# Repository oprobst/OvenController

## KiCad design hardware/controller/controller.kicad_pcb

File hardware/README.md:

# Hardware

KiCad-Projekte des Ofen-Controllers. Entscheidungen und Begründungen:
`specs/002-controller-pcb/plan.md` und `research.md`, Werkzeugwahl: `docs/werkzeuge-pcb.md`.

| Verzeichnis | Inhalt |
|---|---|
| `lib/` | projekteigene Symbole (`oven.kicad_sym`) und Footprints (`oven.pretty/`), Prüfliste in `lib/README.md` |
| `controller/` | Hauptplatine REV A: Schaltplan (`controller.kicad_sch` + 2 Blätter: `controller_leistung` (A3: Netzteil, Sicherheit, Last) und `controller_steuerung` (A2: MCU, USB, Thermoelemente, Bedienung)), Platine, Designregeln, Referenznetzliste `controller.ref.net`, Exporte in `output/` |
| `encoder-carrier/` | Encoder-Träger REV A, gleiche Struktur |
| `tools/` | Prüf- und Hilfsskripte (siehe unten) |
| `archive/skidl/` | früherer Schaltplan als SKiDL-Code (nur noch Archiv) |

## Werkzeugkette

- **Quelle ist der KiCad-10-Schaltplan.** KiCad 10.0.3 unter `D:\hobby\Elektronik\KiCad\10.0`,
  Kommandozeile `D:\hobby\Elektronik\KiCad\10.0\bin\kicad-cli.exe`.
- Die Schaltpläne wurden einmalig aus dem SKiDL-Code (`archive/skidl/`) als Vorlage erzeugt; die
  damals geprüfte Netzliste ist als `<platine>.ref.net` eingefroren.
- Die Platine wird in KiCad aus dem Schaltplan aktualisiert (PCB-Editor: Werkzeuge → „Platine
  aus Schaltplan aktualisieren", F8).
- Die Skripte in `tools/` laufen mit normalem Python (`check_schematic.py`, `make_project.py`)
  oder mit KiCads Python (`D:/hobby/Elektronik/KiCad/10.0/bin/python.exe`, alle mit `pcbnew`).

## KiCad-Projekt anlegen (einmalig je Platine)

```bash
"D:/hobby/Elektronik/KiCad/10.0/bin/python.exe" hardware/tools/make_board.py hardware/controller/controller.kicad_pcb
```

```bash
python hardware/tools/make_project.py hardware/controller/controller.kicad_pro
```

Reihenfolge einhalten: Das Speichern einer neuen Platine setzt die Projektdatei zurück.
`make_project.py` setzt die Netzklassen `Mains` (L_IN, N_IN, L_FUSED), `Power` und `Default`
und die Mindestwerte. Die Sicherheitsabstände stehen als eigene Regeln in
`controller/controller.kicad_dru`: Netz ↔ Kleinspannung 6 mm (Luft- und Kriechstrecke), L ↔ N
3 mm, keine Vias in Netzleitungen, Netz ↔ Platinenrand 3 mm, Netz ↔ Montagelöcher 3 mm. Die
ersten vier Regeln sind an einer Testplatine mit absichtlichen Verstößen geprüft (T019), die
Regel zu den Montagelöchern wird mit dem ersten Layout geprüft. `controller/fp-lib-table` bindet
`hardware/lib/oven.pretty` für die KiCad-Oberfläche ein.

## Schaltplan prüfen (nach jeder Änderung)

```bash
python hardware/tools/check_schematic.py controller
```

```bash
python hardware/tools/check_schematic.py encoder-carrier
```

Exportiert die Netzliste des Schaltplans mit `kicad-cli` und vergleicht sie mit der
Referenznetzliste: Bauteile (Referenz, Wert, Footprint, MPN, DNP), Verbindungen (welche Pins
zusammenhängen, unabhängig vom Netznamen), Netznamen am ESP32 und an allen Netzen mit Netzklasse
(`Mains`, `Power` aus der `.kicad_pro`). Bei der Hauptplatine zusätzlich der GPIO-Abgleich mit
`firmware/include/board/board_rev_a.h`. Exit-Code 1 bei jeder Abweichung, umbenannte Netze ohne
Netzklasse sind nur Hinweise.

**Gewollte Schaltungsänderung:** Schaltplan ändern, ERC, dann die Referenznetzliste im selben
Commit neu exportieren und den Grund in der Commit-Nachricht nennen:

```bash
"D:/hobby/Elektronik/KiCad/10.0/bin/kicad-cli.exe" sch export netlist --output hardware/controller/controller.ref.net hardware/controller/controller.kicad_sch
```

ERC des Schaltplans:

```bash
"D:/hobby/Elektronik/KiCad/10.0/bin/kicad-cli.exe" sch erc --exit-code-violations --output hardware/controller/output/erc.rpt hardware/controller/controller.kicad_sch
```

## Schaltplan und Platine abgleichen

Normalerweise in KiCad mit F8. Skriptweise (z. B. nach dem Wechsel der Quelle):

```bash
"D:/hobby/Elektronik/KiCad/10.0/bin/kicad-cli.exe" sch export netlist --output hardware/controller/output/controller.net hardware/controller/controller.kicad_sch
```

```bash
"D:/hobby/Elektronik/KiCad/10.0/bin/python.exe" hardware/tools/import_netlist.py hardware/controller/output/controller.net hardware/controller/controller.kicad_pcb
```

Hat ein Symbol eine neue UUID bekommen (z. B. nach Ersetzen oder Einfügen in KiCad), verknüpft das
Skript den Footprint über die Referenz neu, statt ihn zu löschen; die Platzierung bleibt erhalten
und jede Neuverknüpfung wird ausgegeben. Die Montagelöcher H1–H4
sind „nur Platine" und haben kein Symbol. Der DRC mit `--schematic-parity` prüft, dass Platine
und Schaltplan zusammenpassen.

Die Vorplatzierung (`tools/place_controller.py`) lief einmalig für REV A und verweigert einen
zweiten Lauf, sobald ein Platinenumriss existiert.

Die Netzabdeckung ist auf der Platine der Footprint COV1 (`oven:Netzabdeckung_REVA`, nur
Platine, im Ursprung platziert). Er wird aus Parametern erzeugt; nach Änderungen an Wandlage oder
Schraubenlöchern das Skript anpassen, neu erzeugen und in KiCad „Footprints aus Bibliothek
aktualisieren“:

```bash
"D:/hobby/Elektronik/KiCad/10.0/bin/python.exe" hardware/tools/make_cover_footprint.py
```

## Prüfen und exportieren

```bash
"D:/hobby/Elektronik/KiCad/10.0/bin/kicad-cli.exe" pcb drc --schematic-parity --exit-code-violations --output hardware/controller/output/drc.rpt hardware/controller/controller.kicad_pcb
```

```bash
"D:/hobby/Elektronik/KiCad/10.0/bin/kicad-cli.exe" pcb export gerbers --output hardware/controller/output/gerber/ hardware/controller/controller.kicad_pcb
```

```bash
"D:/hobby/Elektronik/KiCad/10.0/bin/kicad-cli.exe" pcb export drill --output hardware/controller/output/gerber/ hardware/controller/controller.kicad_pcb
```

```bash
"D:/hobby/Elektronik/KiCad/10.0/bin/kicad-cli.exe" pcb export pos --output hardware/controller/output/controller-pos.csv hardware/controller/controller.kicad_pcb
```

```bash
"D:/hobby/Elektronik/KiCad/10.0/bin/kicad-cli.exe" pcb export step --output hardware/controller/output/controller.step hardware/controller/controller.kicad_pcb
```

```bash
"D:/hobby/Elektronik/KiCad/10.0/bin/kicad-cli.exe" sch export bom --fields "Reference,Value,Footprint,MPN,Source,QUANTITY,DNP" --group-by "Value,Footprint,MPN" --output hardware/controller/output/controller-bom.csv hardware/controller/controller.kicad_sch
```

## Regeln

- **Jede Pinbelegung und jeden Footprint gegen das Datenblatt prüfen**, bevor er verwendet
  wird; geprüfte Teile in `lib/README.md` eintragen. KI-Werkzeuge machen hier typischerweise
  Fehler.
- Netzspannung führende Netze gehören zur Netzklasse `Mains`; ihre Abstände prüft der DRC
  (Regeln in `controller/controller.kicad_dru`).
- Keine Test- oder Messpunkte im 230-V-Bereich.
- GPIO-Zuordnung im Schaltplan und in `firmware/include/board/board_rev_a.h` müssen
  übereinstimmen (Verfassung, Prinzip VI); `check_schematic.py` prüft das.
- Netze mit Netzklasse (L_IN, N_IN, L_FUSED, Versorgungen) brauchen im Schaltplan ein Label mit
  genau diesem Namen, sonst fallen sie aus ihrer Netzklasse und damit aus den Abstandsregeln.

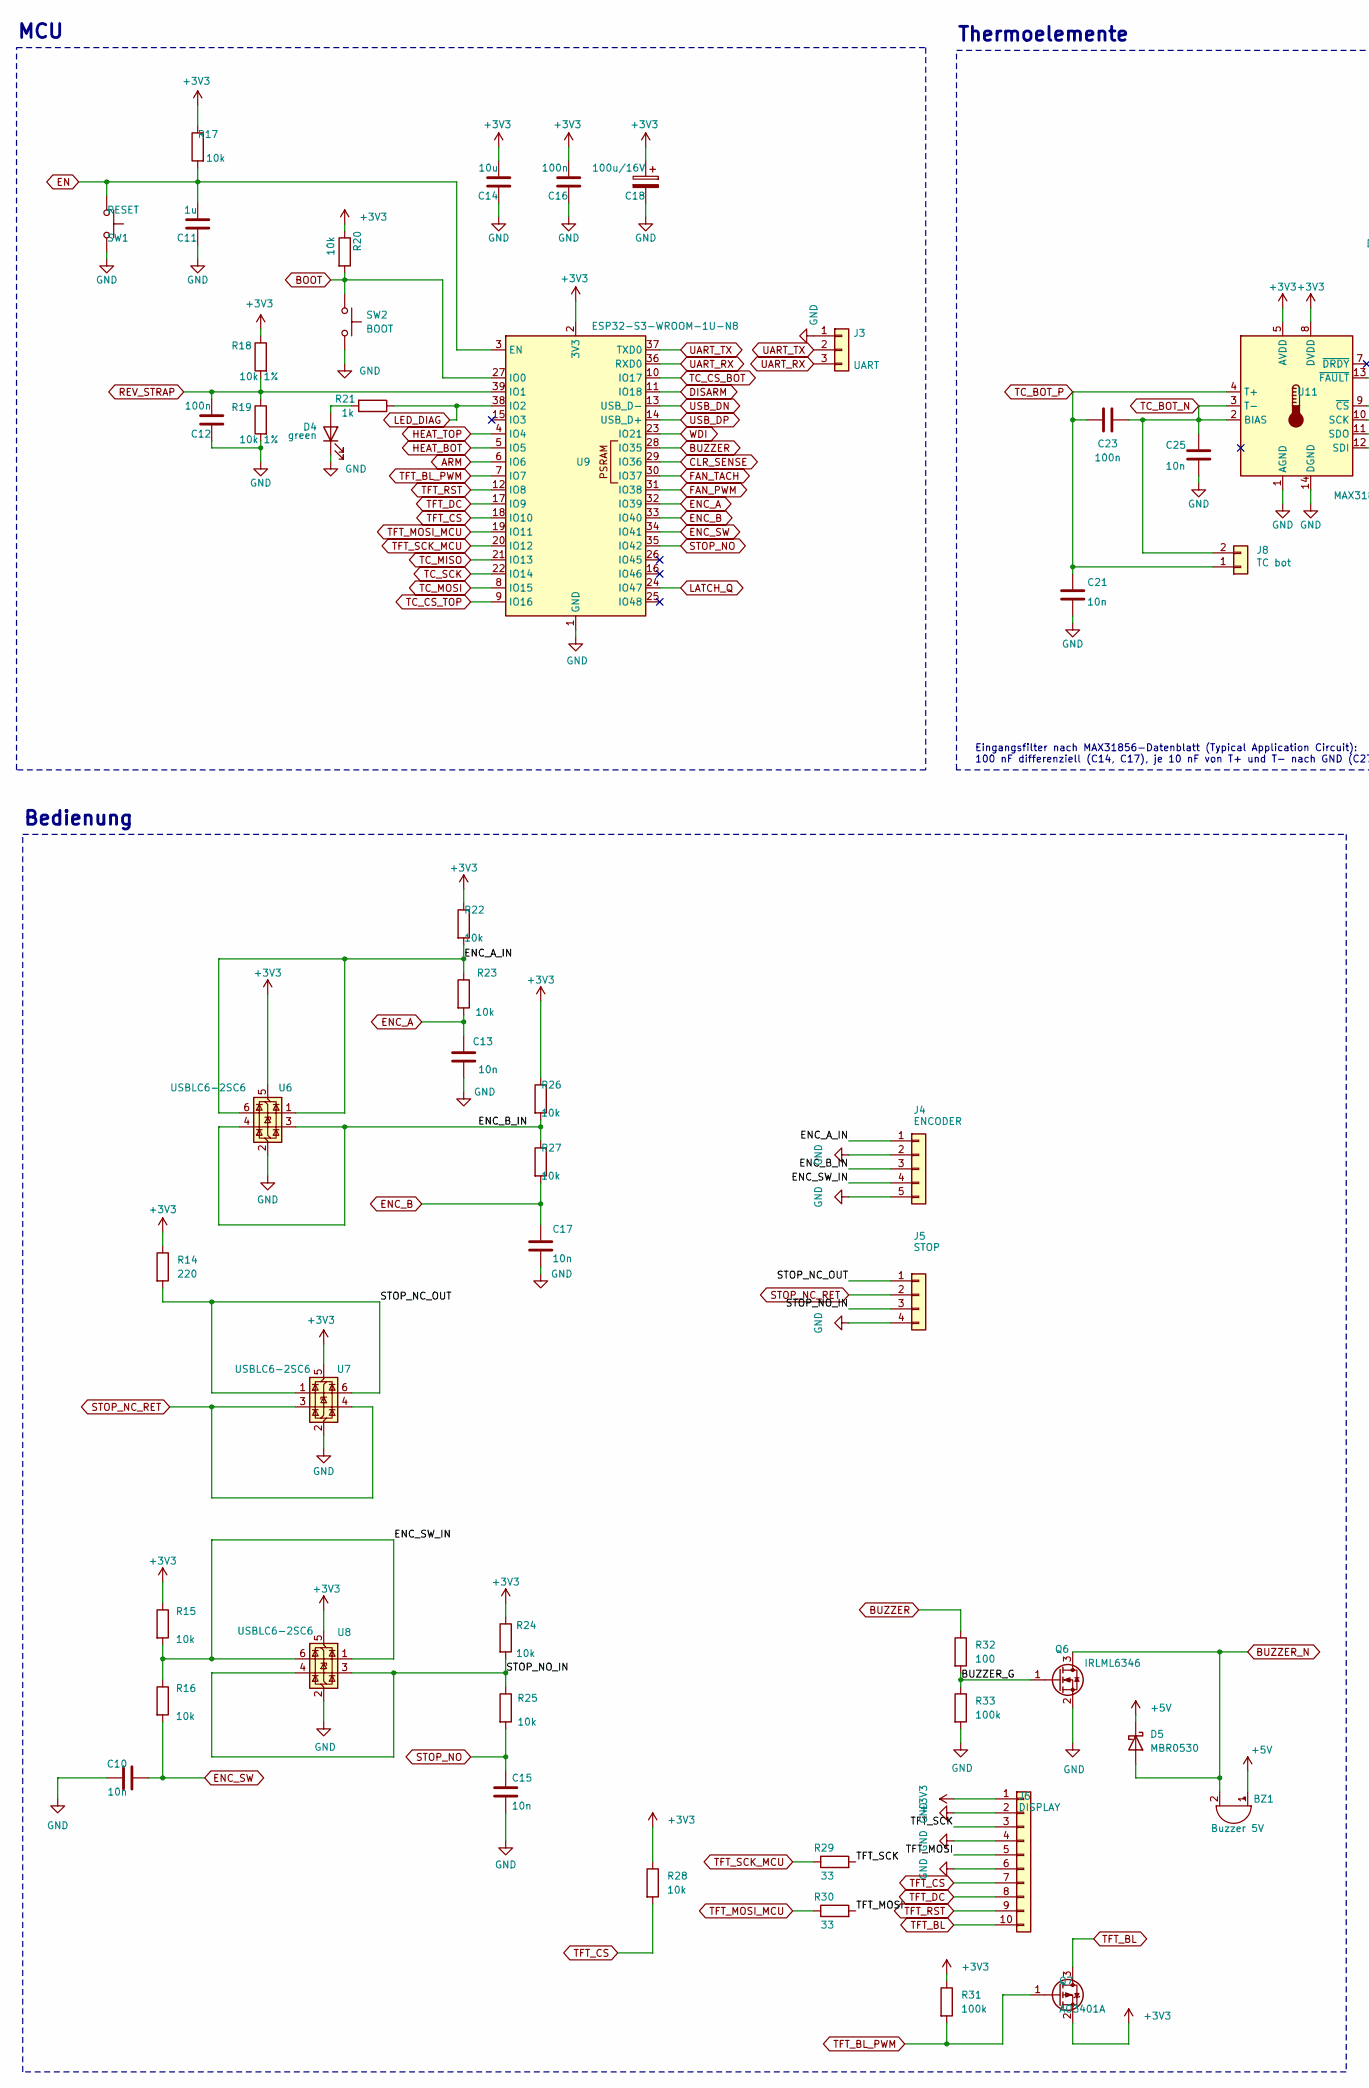
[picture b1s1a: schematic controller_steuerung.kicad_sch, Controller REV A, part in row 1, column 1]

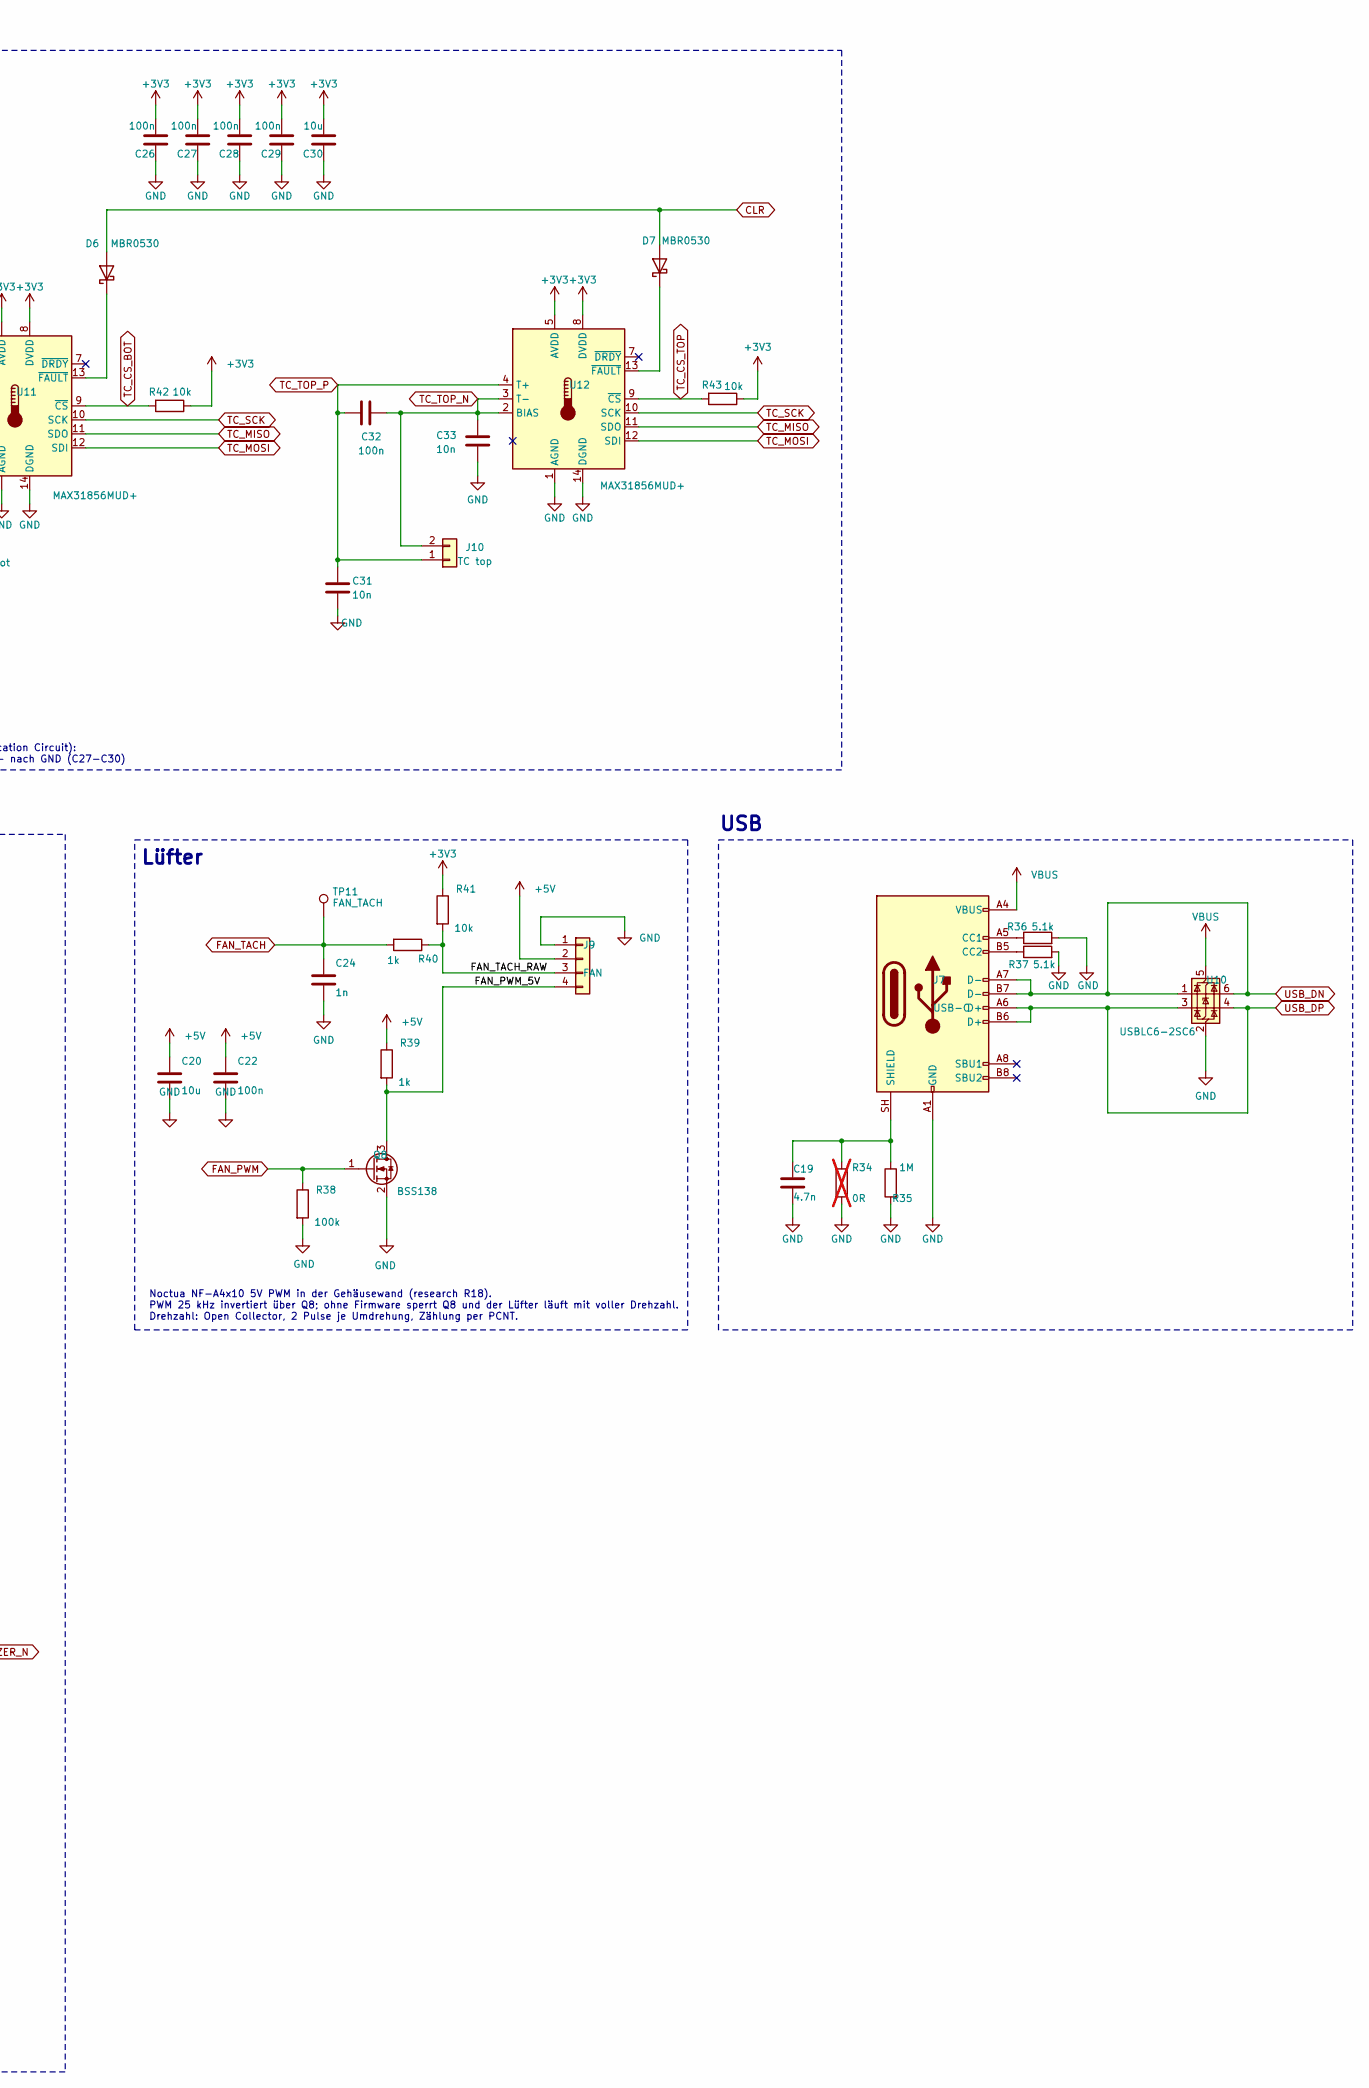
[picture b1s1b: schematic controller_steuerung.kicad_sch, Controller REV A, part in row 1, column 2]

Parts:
BZ1: Buzzer 5V; Buzzer_12x9.5RM7.6; MPN passive magnetic 5 V, >= 70 °C (tbd)
C10, C13, C15, C17, C21, C25, C31, C33: 10n; C_0603_1608Metric
C11: 1u; C_0603_1608Metric
C12, C16, C22, C23, C26, C27, C28, C29, C32: 100n; C_0603_1608Metric
C14, C20, C30: 10u; C_0805_2012Metric
C18: 100u/16V; CP_Radial_D6.3mm_P2.50mm; MPN 105 °C type
C19: 4.7n; C_0603_1608Metric
C24: 1n; C_0603_1608Metric
D4: green; LED_0805_2012Metric
D5, D6, D7: MBR0530; D_SOD-123
J3: UART; PinHeader_1x03_P2.54mm_Vertical
J4: ENCODER; JST_XH_B5B-XH-A_1x05_P2.50mm_Vertical; MPN JST B5B-XH-A
J5: STOP; JST_XH_B4B-XH-A_1x04_P2.50mm_Vertical; MPN JST B4B-XH-A
J6: DISPLAY; JST_XH_B10B-XH-A_1x10_P2.50mm_Vertical; MPN JST B10B-XH-A
J7: USB-C; USB_C_Receptacle_GCT_USB4085; MPN GCT USB4085-GF-A
J8: TC bot; RS_381-7564_Horizontal; MPN RS PRO 381-7564
J9: FAN; FanPinHeader_1x04_P2.54mm_Vertical
J10: TC top; RS_381-7564_Horizontal; MPN RS PRO 381-7564
Q6: IRLML6346; SOT-23; MPN IRLML6346
Q7: AO3401A; SOT-23; MPN AO3401A
Q8: BSS138; SOT-23; MPN BSS138
R14: 220; R_0603_1608Metric
R15, R16, R17, R20, R22, R23, R24, R25, R26, R27, R28, R41, R42, R43: 10k; R_0603_1608Metric
R18, R19: 10k 1%; R_0603_1608Metric
R21, R39, R40: 1k; R_0603_1608Metric
R29, R30: 33; R_0603_1608Metric
R31, R33, R38: 100k; R_0603_1608Metric
R32: 100; R_0603_1608Metric
R34: 0R; R_0603_1608Metric; not fitted
R35: 1M; R_0603_1608Metric
R36, R37: 5.1k; R_0603_1608Metric
SW1: RESET; SW_PUSH_6mm
SW2: BOOT; SW_PUSH_6mm
TP11: FAN_TACH; TestPoint_Keystone_5000-5004_Miniature
U6, U7, U8, U10: USBLC6-2SC6; SOT-23-6; MPN ST USBLC6-2SC6
U9: ESP32-S3-WROOM-1U-N8; ESP32-S3-WROOM-1U; MPN Espressif ESP32-S3-WROOM-1U-N8
U11, U12: MAX31856MUD+; TSSOP-14_4.4x5mm_P0.65mm; MPN Analog Devices MAX31856MUD+

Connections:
+3V3: C14.1, C16.1, C18.1, C26.1, C27.1, C28.1, C29.1, C30.1, J6.1, Q7.2 (S), R14.1, R15.1, R17.1, R18.1, R20.1, R22.1, R24.1, R26.1, R28.1, R31.1, R41.1, R42.1, R43.1, U6.5 (VBUS), U7.5 (VBUS), U8.5 (VBUS), U9.2 (3V3), U11.5 (AVDD), U11.8 (DVDD), U12.5 (AVDD), U12.8 (DVDD); also elsewhere on the board
+5V: BZ1.1 (+), C20.1, C22.1, D5.1 (K), J9.2, R39.1; also elsewhere on the board
/Steuerung und Messung/BUZZER_G: Q6.1 (G), R32.2, R33.1
/Steuerung und Messung/ENC_A_IN: J4.1, R22.2, R23.1, U6.1 (I/O1), U6.6 (I/O1)
/Steuerung und Messung/ENC_B_IN: J4.3, R26.2, R27.1, U6.3 (I/O2), U6.4 (I/O2)
/Steuerung und Messung/ENC_SW_IN: J4.4, R15.2, R16.1, U8.1 (I/O1), U8.6 (I/O1)
/Steuerung und Messung/FAN_PWM_5V: J9.4, Q8.3 (D), R39.2
/Steuerung und Messung/FAN_TACH_RAW: J9.3, R40.1, R41.2
/Steuerung und Messung/STOP_NC_OUT: J5.1, R14.2, U7.1 (I/O1), U7.6 (I/O1)
/Steuerung und Messung/STOP_NO_IN: J5.3, R24.2, R25.1, U8.3 (I/O2), U8.4 (I/O2)
/Steuerung und Messung/TFT_MOSI: J6.5, R30.2
/Steuerung und Messung/TFT_SCK: J6.3, R29.2
ARM: U9.6 (IO6); also elsewhere on the board
BOOT: R20.2, SW2.1, U9.27 (IO0)
BUZZER: R32.1, U9.28 (IO35)
BUZZER_N: BZ1.2 (-), D5.2 (A), Q6.3 (D)
CLR: D6.2 (A), D7.2 (A); also elsewhere on the board
CLR_SENSE: U9.29 (IO36); also elsewhere on the board
DISARM: U9.11 (IO18); also elsewhere on the board
EN: C11.1, R17.2, SW1.1, U9.3 (EN)
ENC_A: C13.1, R23.2, U9.32 (IO39)
ENC_B: C17.1, R27.2, U9.33 (IO40)
ENC_SW: C10.1, R16.2, U9.34 (IO41)
FAN_PWM: Q8.1 (G), R38.1, U9.31 (IO38)
FAN_TACH: C24.1, R40.2, TP11.1 (1_1), U9.30 (IO37)
GND: C10.2, C11.2, C12.2, C13.2, C14.2, C15.2, C16.2, C17.2, C18.2, C19.2, C20.2, C21.2, C22.2, C24.2, C25.2, C26.2, C27.2, C28.2, C29.2, C30.2, C31.2, C33.2, D4.1 (K), J3.1, J4.2, J4.5, J5.4, J6.2, J6.4, J6.6, J7.A1 (GND), J7.A12 (GND), J7.B1 (GND), J7.B12 (GND), J9.1, Q6.2 (S), Q8.2 (S), R19.2, R33.2, R34.2, R35.2, R36.2, R37.2, R38.2, SW1.2, SW2.2, U6.2 (GND), U7.2 (GND), U8.2 (GND), U9.1 (GND), U9.40 (GND), U9.41 (GND), U10.2 (GND), U11.1 (AGND), U11.14 (DGND), U12.1 (AGND), U12.14 (DGND); also elsewhere on the board
HEAT_BOT: U9.5 (IO5); also elsewhere on the board
HEAT_TOP: U9.4 (IO4); also elsewhere on the board
LATCH_Q: U9.24 (IO47); also elsewhere on the board
LED_DIAG: R21.1, U9.38 (IO2)
unnamed: D4.2 (A), R21.2
unnamed: D6.1 (K), U11.13 (~FAULT)
unnamed: D7.1 (K), U12.13 (~FAULT)
unnamed: J7.A5 (CC1), R36.1
unnamed: J7.B5 (CC2), R37.1
unnamed: C19.1, J7.SH (SHIELD), R34.1, R35.1
REV_STRAP: C12.1, R18.2, R19.1, U9.39 (IO1)
STOP_NC_RET: J5.2, U7.3 (I/O2), U7.4 (I/O2); also elsewhere on the board
STOP_NO: C15.1, R25.2, U9.35 (IO42)
TC_BOT_N: C23.2, C25.1, J8.2, U11.2 (BIAS), U11.3 (T-)
TC_BOT_P: C21.1, C23.1, J8.1, U11.4 (T+)
TC_CS_BOT: R42.2, U9.10 (IO17), U11.9 (~CS)
TC_CS_TOP: R43.2, U9.9 (IO16), U12.9 (~CS)
TC_MISO: U9.21 (IO13), U11.11 (SDO), U12.11 (SDO)
TC_MOSI: U9.8 (IO15), U11.12 (SDI), U12.12 (SDI)
TC_SCK: U9.22 (IO14), U11.10 (SCK), U12.10 (SCK)
TC_TOP_N: C32.2, C33.1, J10.2, U12.2 (BIAS), U12.3 (T-)
TC_TOP_P: C31.1, C32.1, J10.1, U12.4 (T+)
TFT_BL: J6.10, Q7.3 (D)
TFT_BL_PWM: Q7.1 (G), R31.2, U9.7 (IO7)
TFT_CS: J6.7, R28.2, U9.18 (IO10)
TFT_DC: J6.8, U9.17 (IO9)
TFT_MOSI_MCU: R30.1, U9.19 (IO11)
TFT_RST: J6.9, U9.12 (IO8)
TFT_SCK_MCU: R29.1, U9.20 (IO12)
UART_RX: J3.3, U9.36 (RXD0)
UART_TX: J3.2, U9.37 (TXD0)
USB_DN: J7.A7 (D-), J7.B7 (D-), U9.13 (USB_D-), U10.1 (I/O1), U10.6 (I/O1)
USB_DP: J7.A6 (D+), J7.B6 (D+), U9.14 (USB_D+), U10.3 (I/O2), U10.4 (I/O2)
VBUS: J7.A4 (VBUS), J7.A9 (VBUS), J7.B4 (VBUS), J7.B9 (VBUS), U10.5 (VBUS); also elsewhere on the board
WDI: U9.23 (IO21); also elsewhere on the board

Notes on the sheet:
Noctua NF-A4x10 5V PWM in der Gehäusewand (research R18). PWM 25 kHz invertiert über Q8; ohne Firmware sperrt Q8 und der Lüfter läuft mit voller Drehzahl. Drehzahl: Open Collector, 2 Pulse je Umdrehung, Zählung per PCNT.
Eingangsfilter nach MAX31856-Datenblatt (Typical Application Circuit): 100 nF differenziell (C14, C17), je 10 nF von T+ und T- nach GND (C27-C30)
Thermoelemente
Lüfter
Bedienung
USB
MCU

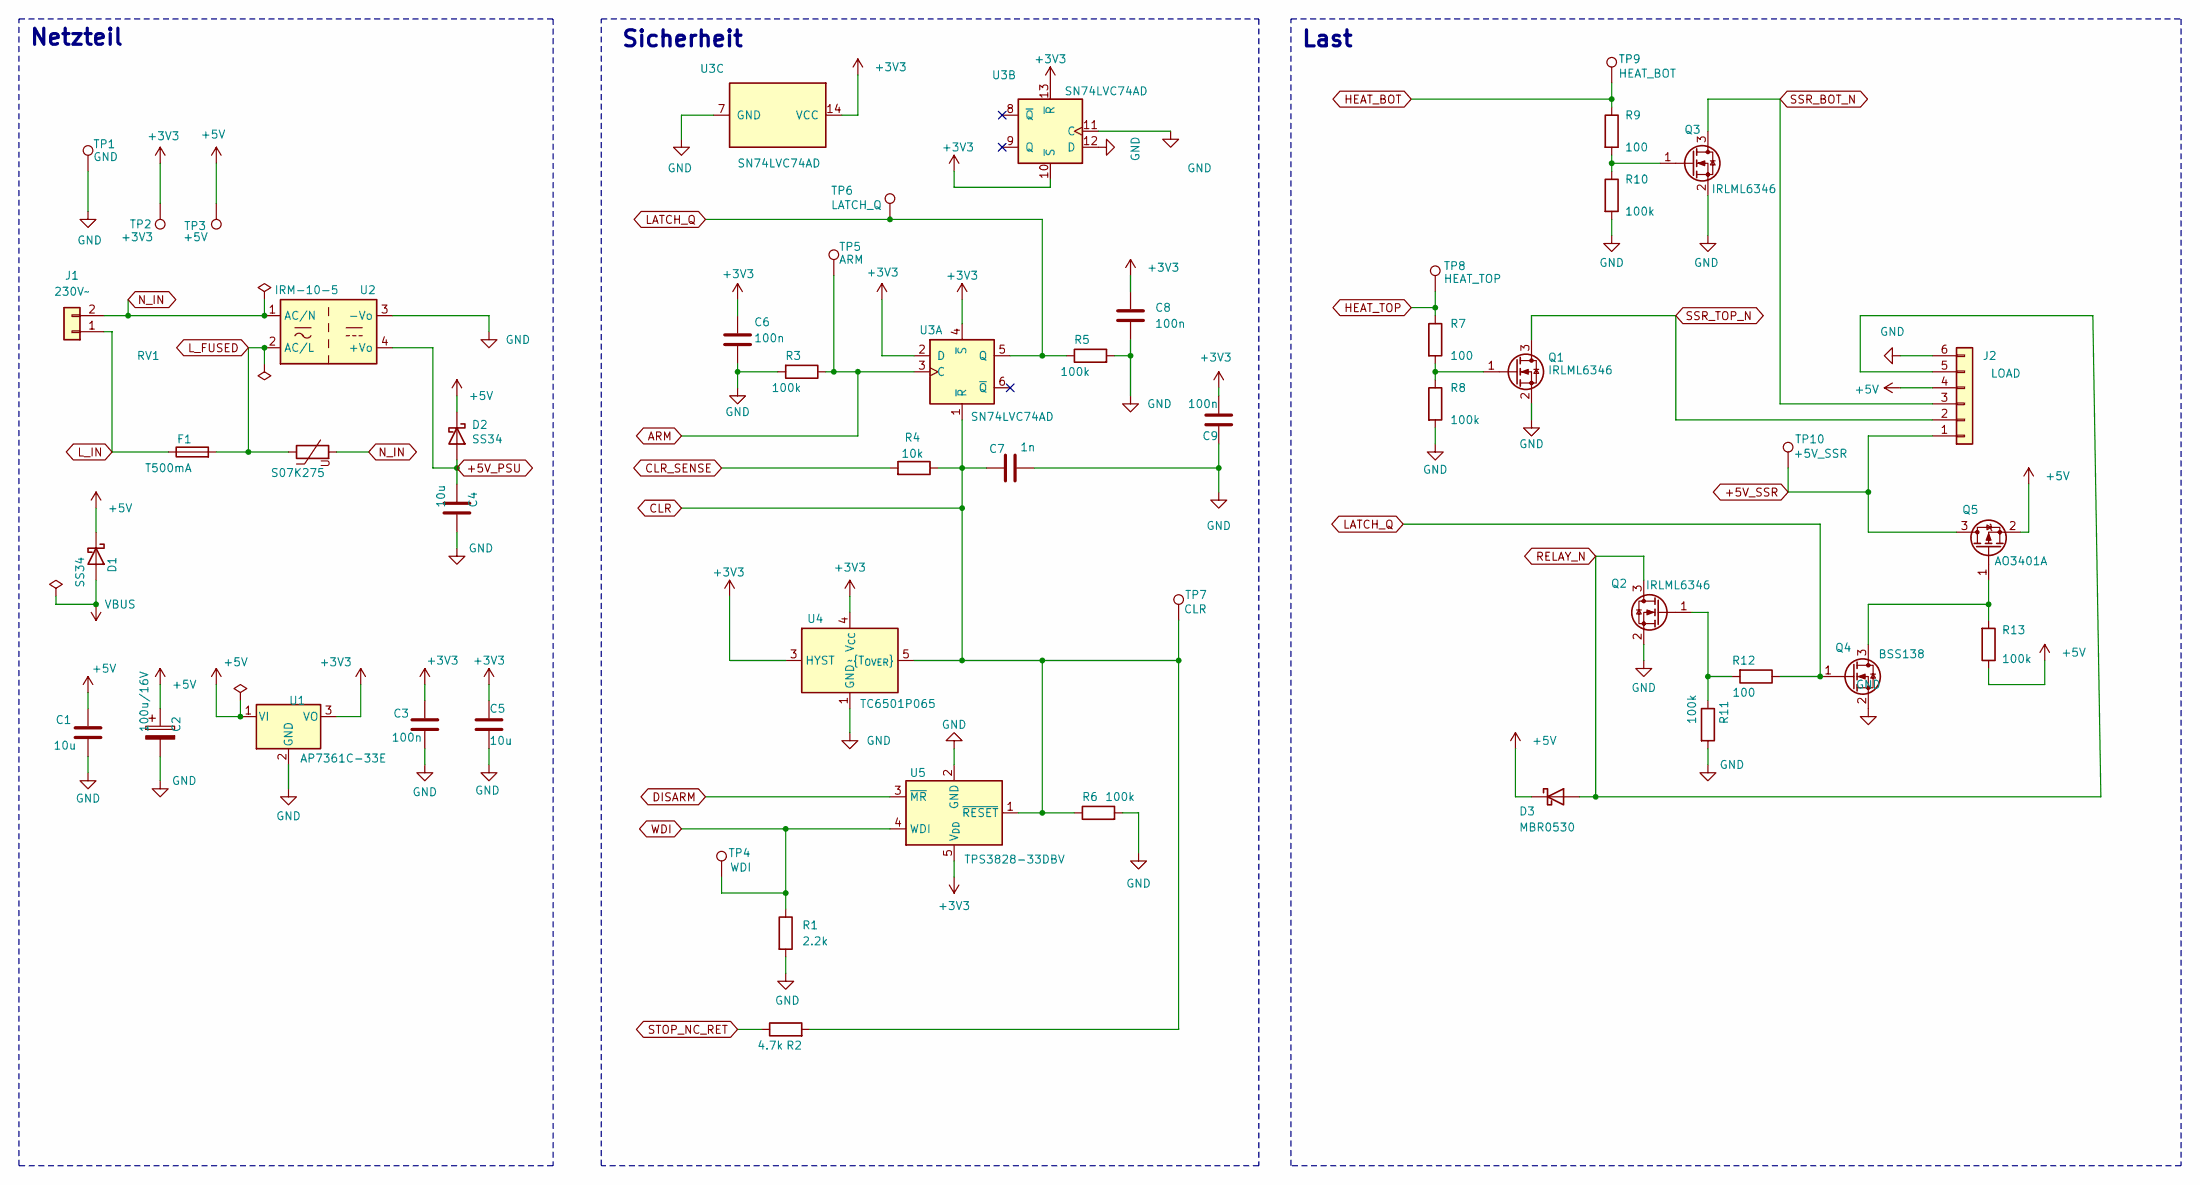
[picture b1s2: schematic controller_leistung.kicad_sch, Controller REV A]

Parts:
C1, C4, C5: 10u; C_0805_2012Metric
C2: 100u/16V; CP_Radial_D6.3mm_P2.50mm; MPN 105 °C type
C3, C6, C8, C9: 100n; C_0603_1608Metric
C7: 1n; C_0603_1608Metric
D1, D2: SS34; D_SMA
D3: MBR0530; D_SOD-123
F1: T500mA; Fuseholder_Cylinder-5x20mm_Schurter_0031_8201_Horizontal_Op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; MPN Schurter OGN 0031.8201 + 5x20 T500mA
J1: 230V~; Phoenix_MKDS-1,5-2-5.08_Horizontal_OvalPads; MPN Phoenix MKDS 1,5/2-5,08
J2: LOAD; Phoenix_MKDS-1-6-3.81_Horizontal_OvalPads; MPN Phoenix MKDS 1/6-3,81
Q1, Q2, Q3: IRLML6346; SOT-23; MPN IRLML6346
Q4: BSS138; SOT-23; MPN BSS138
Q5: AO3401A; SOT-23; MPN AO3401A
R1: 2.2k; R_0603_1608Metric
R2: 4.7k; R_0603_1608Metric
R3, R5, R6, R8, R10, R11, R13: 100k; R_0603_1608Metric
R4: 10k; R_0603_1608Metric
R7, R9, R12: 100; R_0603_1608Metric
RV1: S07K275; RV_Disc_D7mm_W3.4mm_P5mm; MPN TDK B72207S2271K101
TP1: GND; TestPoint_Keystone_5000-5004_Miniature
TP2: +3V3; TestPoint_Keystone_5000-5004_Miniature
TP3: +5V; TestPoint_Keystone_5000-5004_Miniature
TP4: WDI; TestPoint_Keystone_5000-5004_Miniature
TP5: ARM; TestPoint_Keystone_5000-5004_Miniature
TP6: LATCH_Q; TestPoint_Keystone_5000-5004_Miniature
TP7: CLR; TestPoint_Keystone_5000-5004_Miniature
TP8: HEAT_TOP; TestPoint_Keystone_5000-5004_Miniature
TP9: HEAT_BOT; TestPoint_Keystone_5000-5004_Miniature
TP10: +5V_SSR; TestPoint_Keystone_5000-5004_Miniature
U1: AP7361C-33E; SOT-223-3_TabPin2; MPN Diodes AP7361C-33E-13
U2: IRM-10-5; Converter_ACDC_MeanWell_IRM-10-xx_THT; MPN Mean Well IRM-10-5
U3: SN74LVC74AD; SOIC-14_3.9x8.7mm_P1.27mm; MPN TI SN74LVC74AD
U4: TC6501P065; SOT-23-5; MPN Microchip TC6501P065VCTTR
U5: TPS3828-33DBV; SOT-23-5; MPN TI TPS3828-33DBVR

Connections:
+3V3: C3.1, C5.1, C6.1, C8.1, C9.1, TP2.1 (1_1), U1.3 (VO), U3.2 (D), U3.4 (~S), U3.10 (~S), U3.13 (~R), U3.14 (VCC), U4.3 (HYST), U4.4 (V_{CC}), U5.5 (V_{DD}); also elsewhere on the board
+5V: C1.1, C2.1, D1.1 (K), D2.1 (K), D3.1 (K), J2.4, Q5.2 (S), R13.1, TP3.1 (1_1), U1.1 (VI); also elsewhere on the board
+5V_PSU: C4.1, D2.2 (A), U2.4 (+Vo)
+5V_SSR: J2.1, Q5.3 (D), TP10.1 (1_1)
ARM: R3.1, TP5.1 (1_1), U3.3 (C); also elsewhere on the board
CLR: C7.1, R2.2, R4.1, R6.1, TP7.1 (1_1), U3.1 (~R), U4.5 (~T_{OVER}), U5.1 (~RESET); also elsewhere on the board
CLR_SENSE: R4.2; also elsewhere on the board
DISARM: U5.3 (~MR); also elsewhere on the board
GND: C1.2, C2.2, C3.2, C4.2, C5.2, C6.2, C7.2, C8.2, C9.2, J2.6, Q1.2 (S), Q2.2 (S), Q3.2 (S), Q4.2 (S), R1.2, R3.2, R5.2, R6.2, R8.2, R10.2, R11.2, TP1.1 (1_1), U1.2 (GND), U2.3 (-Vo), U3.7 (GND), U3.11 (C), U3.12 (D), U4.1 (GND), U4.2 (GND), U5.2 (GND); also elsewhere on the board
HEAT_BOT: R9.1, TP9.1 (1_1); also elsewhere on the board
HEAT_TOP: R7.1, TP8.1 (1_1); also elsewhere on the board
LATCH_Q: Q4.1 (G), R5.1, R12.1, TP6.1 (1_1), U3.5 (Q); also elsewhere on the board
L_FUSED: F1.2, RV1.1, U2.2 (AC/L)
L_IN: F1.1, J1.1
N_IN: J1.2, RV1.2, U2.1 (AC/N)
unnamed: Q1.1 (G), R7.2, R8.1
unnamed: Q2.1 (G), R11.1, R12.2
unnamed: Q3.1 (G), R9.2, R10.1
unnamed: Q4.3 (D), Q5.1 (G), R13.2
RELAY_N: D3.2 (A), J2.5, Q2.3 (D)
SSR_BOT_N: J2.3, Q3.3 (D)
SSR_TOP_N: J2.2, Q1.3 (D)
STOP_NC_RET: R2.1; also elsewhere on the board
VBUS: D1.2 (A); also elsewhere on the board
WDI: R1.1, TP4.1 (1_1), U5.4 (WDI); also elsewhere on the board

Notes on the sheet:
Netzteil
Last
Sicherheit

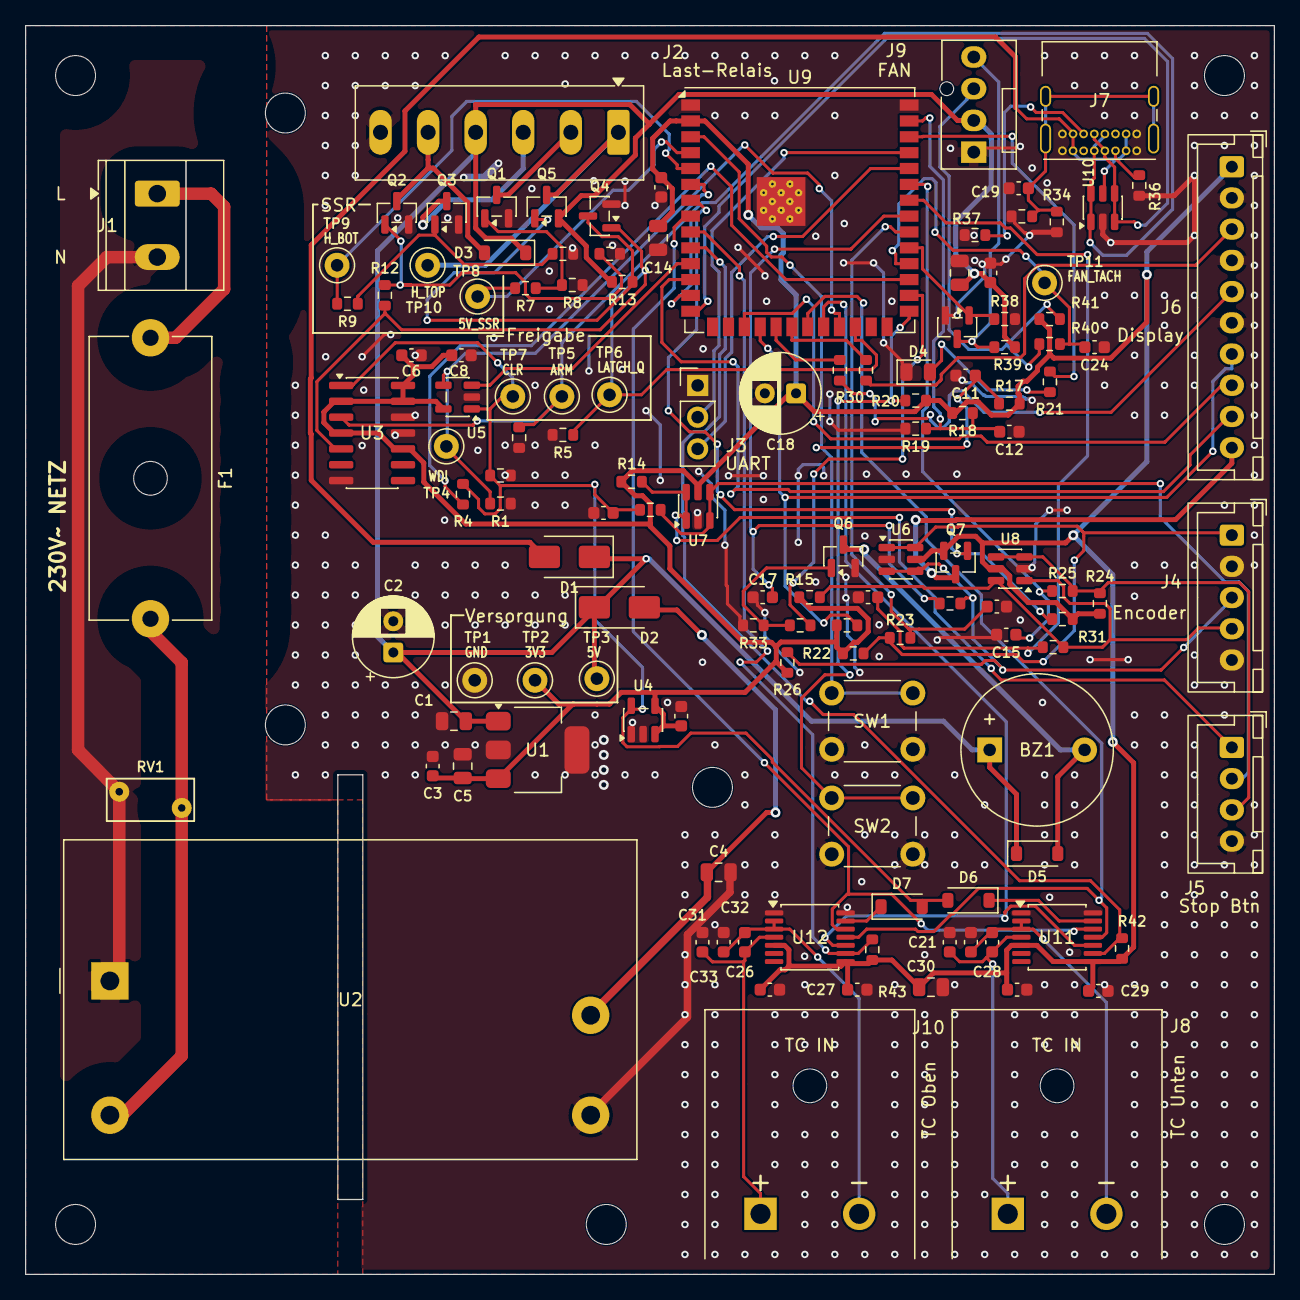
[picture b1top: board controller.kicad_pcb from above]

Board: 2 copper layers, 100.0 x 100.0 mm, 134 parts (0 on the bottom side), 73 nets.

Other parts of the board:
COV1: Netzabdeckung_REVA
H1, H2, H3, H4: MountingHole_3.2mm_M3

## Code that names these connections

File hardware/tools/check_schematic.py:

"""Checks a KiCad schematic against the frozen reference netlist and the firmware board header.

Usage (normal Python; kicad-cli is called for the export):
    python hardware/tools/check_schematic.py controller
    python hardware/tools/check_schematic.py encoder-carrier

0. Checks the file format of every sheet (no raw newline inside a quoted string).
1. Exports the netlist of hardware/<board>/<board>.kicad_sch with kicad-cli.
2. Compares it with hardware/<board>/<board>.ref.net (the netlist verified in feature 002,
   generated from the former SKiDL source):
   - parts: same references, values, footprints, MPN and DNP
   - connectivity: the same pins are connected together (net names may differ)
   - net names at the ESP32 pins must match (the firmware pin check depends on them)
   - net names that select a net class in <board>.kicad_pro (Mains, Power) must match: an
     unnamed mains net would silently lose the 6 mm / 3 mm clearance rules
3. Controller only: every kPin* constant in firmware/include/board/board_rev_a.h must sit on the
   expected net at the ESP32 (constitution principle VI).

Exit code 1 on any difference; every difference is listed. Renamed nets elsewhere are reported
as notes. A deliberate change of the circuit means: update the reference netlist in the same
commit, with the reason in the commit message.
"""

import fnmatch
import json
import re
import subprocess
import sys
import tempfile
from pathlib import Path

sys.path.insert(0, str(Path(__file__).resolve().parent))
from sexp import children, parse_sexp, value  # noqa: E402

REPO = Path(__file__).resolve().parents[2]
KICAD_CLI = Path(r"D:\hobby\Elektronik\KiCad\10.0\bin\kicad-cli.exe")
BOARD_HEADER = REPO / "firmware" / "include" / "board" / "board_rev_a.h"
MCU_REF = "U9"

# ESP32-S3-WROOM-1/1U module pin per GPIO (Espressif datasheet v1.8, table 3-1).
MODULE_PIN = {
    4: 4, 5: 5, 6: 6, 7: 7, 15: 8, 16: 9, 17: 10, 18: 11, 8: 12, 19: 13, 20: 14, 3: 15,
    46: 16, 9: 17, 10: 18, 11: 19, 12: 20, 13: 21, 14: 22, 21: 23, 47: 24, 48: 25, 45: 26,
    0: 27, 35: 28, 36: 29, 37: 30, 38: 31, 39: 32, 40: 33, 41: 34, 42: 35, 44: 36, 43: 37,
    2: 38, 1: 39,
}

# Firmware constant -> net at the ESP32 pin of that GPIO.
HEADER_TO_NET = {
    "kPinRevisionStrap": "REV_STRAP", "kPinDiagLed": "LED_DIAG", "kPinHeatTop": "HEAT_TOP",
    "kPinHeatBottom": "HEAT_BOT", "kPinArm": "ARM", "kPinDisarm": "DISARM",
    "kPinWatchdogWdi": "WDI", "kPinClearSense": "CLR_SENSE", "kPinStopNo": "STOP_NO",
    "kPinLatchQ": "LATCH_Q", "kPinTftBacklight": "TFT_BL_PWM", "kPinTftRst": "TFT_RST",
    "kPinTftDc": "TFT_DC", "kPinTftCs": "TFT_CS", "kPinSpiMosi": "TFT_MOSI_MCU",
    "kPinSpiSck": "TFT_SCK_MCU", "kPinThermocoupleMiso": "TC_MISO",
    "kPinThermocoupleSck": "TC_SCK", "kPinThermocoupleMosi": "TC_MOSI",
    "kPinThermocoupleCsTop": "TC_CS_TOP", "kPinThermocoupleCsBottom": "TC_CS_BOT",
    "kPinBuzzer": "BUZZER", "kPinEncoderA": "ENC_A", "kPinEncoderB": "ENC_B",
    "kPinEncoderButton": "ENC_SW", "kPinFanTach": "FAN_TACH", "kPinFanPwm": "FAN_PWM",
}


def short(name):
    """Net name without the sheet path, e.g. '/Sicherheit/CLR' -> 'CLR'."""
    return name.rsplit("/", 1)[-1] if name else name


def read_netlist(path):
    root = parse_sexp(Path(path).read_text(encoding="utf-8"))
    parts = {}
    for comp in children(children(root, "components")[0], "comp"):
        fields = {}
        for f in children(children(comp, "fields")[0], "field") if children(comp, "fields") else []:
            if len(f) > 2 and isinstance(f[2], str):
                fields[value(f, "name")] = f[2]
        parts[value(comp, "ref")] = (value(comp, "value"), value(comp, "footprint"),
                                     fields.get("MPN", ""), fields.get("DNP", ""))
    nets = {}
    for net in children(children(root, "nets")[0], "net"):
        nodes = frozenset((value(n, "ref"), value(n, "pin")) for n in children(net, "node"))
        if len(nodes) > 1:  # single pins (no-connects) carry no connectivity
            nets[nodes] = short(value(net, "name"))
    return parts, nets


def export_netlist(sch, out):
    subprocess.run([str(KICAD_CLI), "sch", "export", "netlist", "--output", str(out), str(sch)],
                   check=True, capture_output=True)


def netclass_patterns(board_dir, board):
    pro = board_dir / f"{board}.kicad_pro"
    if not pro.exists():
        return []
    patterns = json.loads(pro.read_text(encoding="utf-8"))["net_settings"].get("netclass_patterns") or []
    return [(p["pattern"], p["netclass"]) for p in patterns]


def compare(ref, sch, patterns):
    errors, notes = [], []
    ref_parts, ref_nets = ref
    sch_parts, sch_nets = sch
    for r in sorted(ref_parts.keys() - sch_parts.keys()):
        errors.append(f"part missing in schematic: {r} {ref_parts[r][0]}")
    for r in sorted(sch_parts.keys() - ref_parts.keys()):
        errors.append(f"extra part in schematic: {r} {sch_parts[r][0]}")
    labels = ("value", "footprint", "MPN", "DNP")
    for r in sorted(ref_parts.keys() & sch_parts.keys()):
        for label, a, b in zip(labels, ref_parts[r], sch_parts[r]):
            if a != b:
                errors.append(f"{r}: {label} '{b}' in schematic, '{a}' in reference")

    pin_net = {pin: nodes for nodes in sch_nets for pin in nodes}
    for nodes, name in sorted(ref_nets.items(), key=lambda kv: kv[1]):
        if nodes in sch_nets:
            if sch_nets[nodes] != name:
                msg = f"net {name} is called {sch_nets[nodes]} in the schematic"
                classes = [cls for pat, cls in patterns if fnmatch.fnmatchcase(name, pat)]
                if classes:
                    errors.append(f"{msg}: loses net class {classes[0]}")
                elif any(ref == MCU_REF for ref, _ in nodes):
                    errors.append(msg)
                else:
                    notes.append(msg)
            continue
        groups = {pin_net.get(p) for p in nodes}
        detail = ", ".join(f"{r}.{p}" for r, p in sorted(nodes))
        if len(groups) > 1 or None in groups:
            errors.append(f"net {name} is split or incomplete in the schematic: {detail}")
        else:
            extra = sorted(next(iter(groups)) - nodes)
            errors.append(f"net {name} has extra pins in the schematic: "
                          + ", ".join(f"{r}.{p}" for r, p in extra))
    return errors, notes


def check_board_header(sch_nets):
    header = BOARD_HEADER.read_text(encoding="utf-8")
    pins = {m.group(1): int(m.group(2))
            for m in re.finditer(r"constexpr int8_t (kPin\w+) = (\d+);", header)}
    at_pin = {pin: name for nodes, name in sch_nets.items() for pin in nodes}
    errors = []
    for const, gpio in pins.items():
        expected = HEADER_TO_NET.get(const)
        actual = at_pin.get((MCU_REF, str(MODULE_PIN[gpio])))
        if expected is None:
            errors.append(f"{const} = {gpio}: no expected net in check_schematic.py")
        elif actual != expected:
            errors.append(f"{const} = GPIO {gpio}: header expects net {expected}, schematic has {actual}")
    for const in HEADER_TO_NET.keys() - pins.keys():
        errors.append(f"{const} missing in {BOARD_HEADER.name}")
    return errors


def open_string_lines(text):
    """Line numbers where a quoted string is still open. kicad-cli accepts raw newlines inside
    strings, the KiCad editor refuses to load the sheet."""
    bad, inside, escaped = [], False, False
    for lineno, line in enumerate(text.split("\n"), start=1):
        for ch in line:
            if escaped:
                escaped = False
            elif ch == "\\":
                escaped = True
            elif ch == '"':
                inside = not inside
        if inside:
            bad.append(lineno)
    return bad


def main(board):
    board_dir = REPO / "hardware" / board
    format_errors = []
    for sheet in sorted(board_dir.glob("*.kicad_sch")):
        lines = open_string_lines(sheet.read_text(encoding="utf-8"))
        if lines:
            format_errors.append(f"{sheet.name}: string not closed on line(s) {lines[:5]} "
                                 "(KiCad cannot open the sheet)")
    with tempfile.TemporaryDirectory() as tmp:
        out = Path(tmp) / f"{board}.net"
        export_netlist(board_dir / f"{board}.kicad_sch", out)
        sch = read_netlist(out)
    ref = read_netlist(board_dir / f"{board}.ref.net")
    errors, notes = compare(ref, sch, netclass_patterns(board_dir, board))
    errors = format_errors + errors
    if board == "controller":
        errors += check_board_header(sch[1])
    for n in notes:
        print("NOTE:", n)
    for e in errors:
        print("ERROR:", e)
    print(f"{board}: {len(sch[0])} parts, {len(sch[1])} nets, {len(errors)} errors, {len(notes)} notes")
    return 1 if errors else 0


if __name__ == "__main__":
    sys.exit(main(sys.argv[1]))
